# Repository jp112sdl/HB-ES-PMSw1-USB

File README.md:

# HB-ES-PMSw1-USB
Homebrew Homematic USB Strom-/Spannungsmesser mit INA219

Benötigt [JP-HB-Devices Addon mind. V 4.2](https://github.com/jp112sdl/JP-HB-Devices-addon/releases)

In der Arduino IDE muss noch folgende Lib eingebunden werden:
- https://github.com/jp112sdl/INA219_WE

### Aktueller Stand (14.03.2021):
- CCU Unterstützung bereitgestellt (Addon V 4.2)
- Sketch lauffähig

### schematischer Schaltungsaufbau

###  🚧 PCB - WORK IN PROGRESS

Projekt-Thread im HomeMatic-Forum: https://homematic-forum.de/forum/viewtopic.php?f=76&t=66307

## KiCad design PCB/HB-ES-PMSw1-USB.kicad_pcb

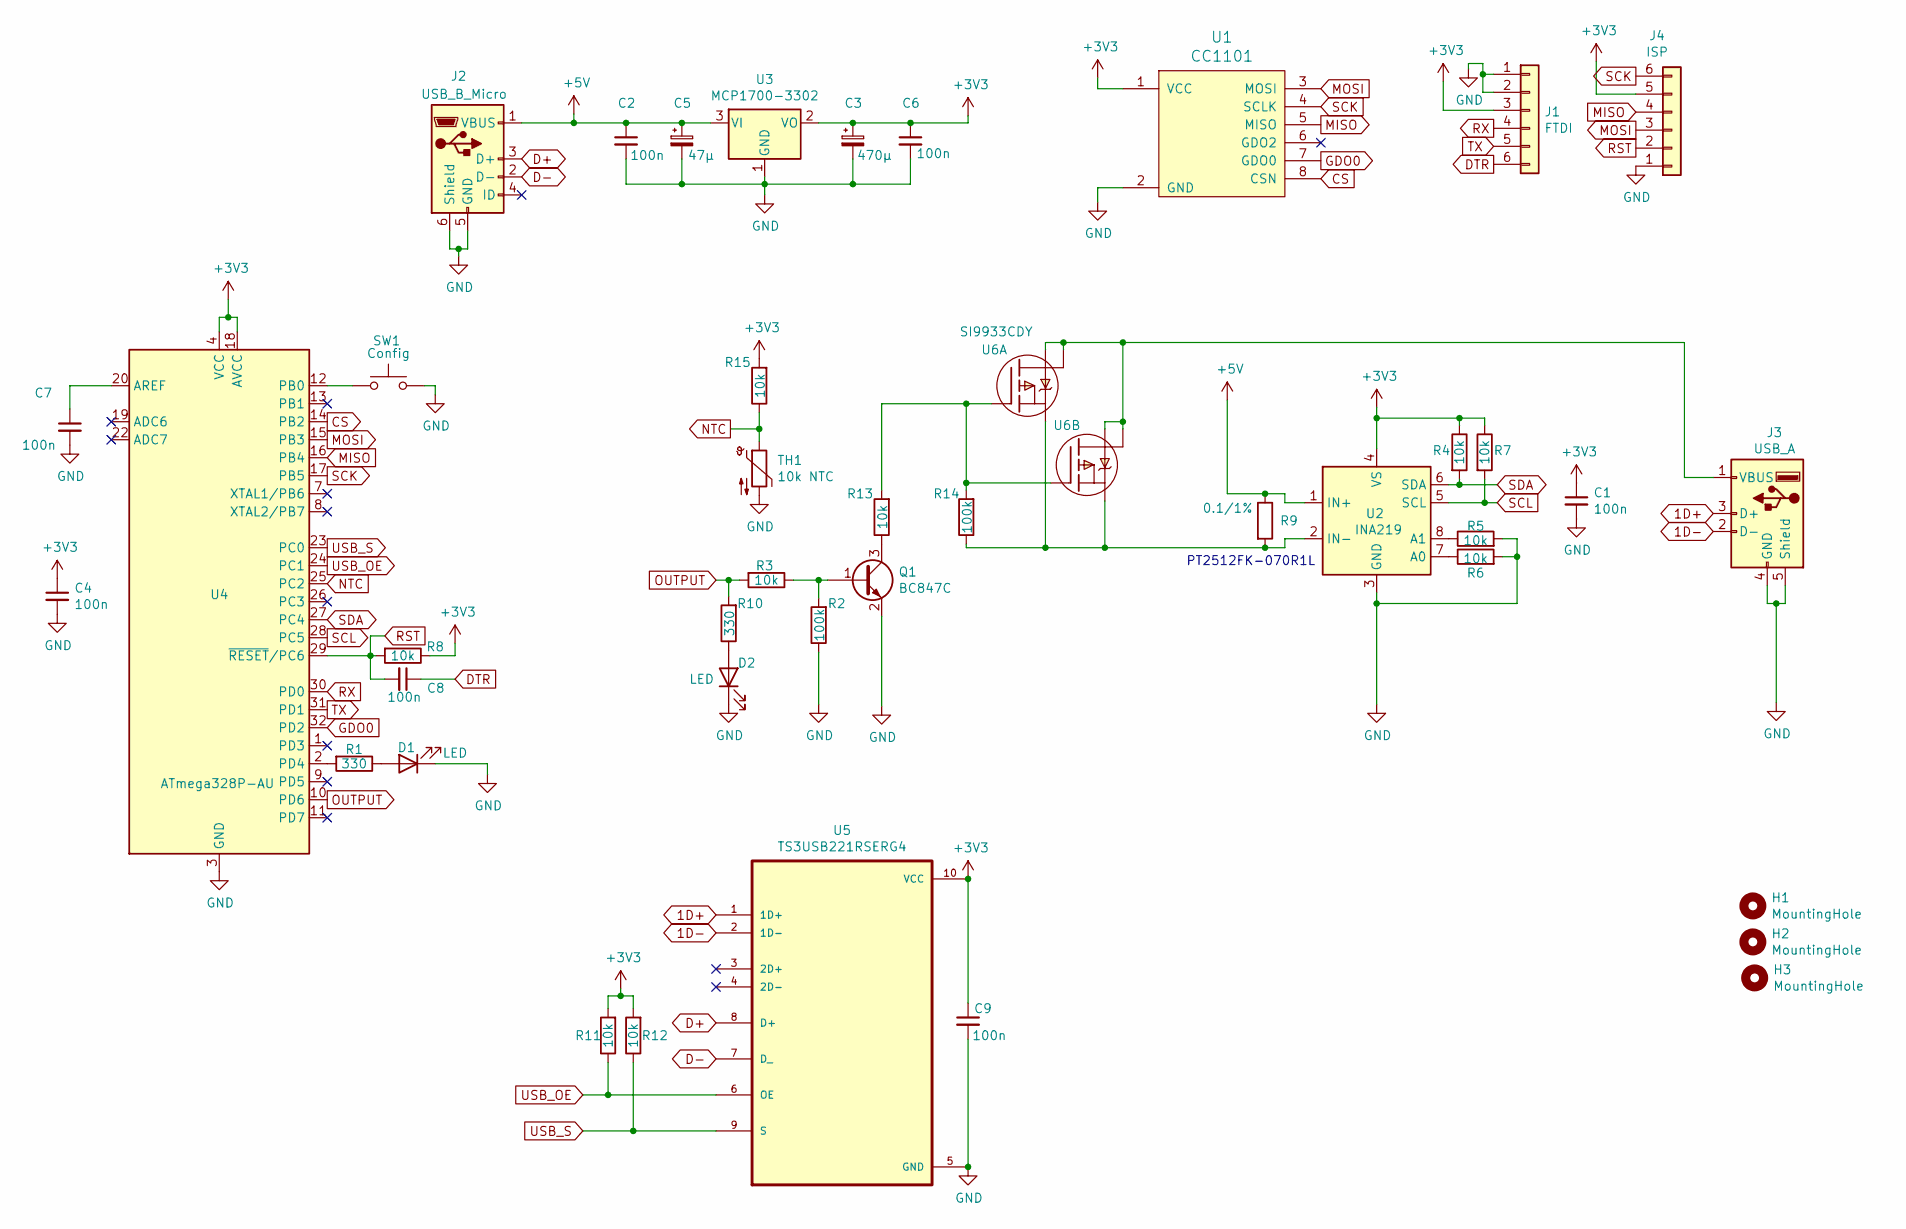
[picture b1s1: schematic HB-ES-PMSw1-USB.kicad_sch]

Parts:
C1, C2, C4, C6, C7, C8, C9: 100n; C_0805_2012Metric_Pad1.15x1.40mm_HandSolder
C3: 470µ; CP_Elec_8x10.5
C5: 47µ; CP_Elec_8x5.4
D1, D2: LED; LED_0805_2012Metric_Pad1.15x1.40mm_HandSolder
H1, H2, H3: MountingHole; MountingHole_2.7mm_M2.5
J1: FTDI; PinHeader_1x06_P2.54mm_Vertical
J2: USB_B_Micro; USB_Micro-B_Molex-105017-0001
J3: USB_A
J4: ISP; PinPads_ISP
Q1: BC847C; SOT-23
R1, R10: 330; R_0805_2012Metric_Pad1.15x1.40mm_HandSolder
R2, R14: 100k; R_0805_2012Metric_Pad1.15x1.40mm_HandSolder
R3, R4, R5, R6, R7, R8, R11, R12, R13, R15: 10k; R_0805_2012Metric_Pad1.15x1.40mm_HandSolder
R9: 0.1/1%; R_2512_6332Metric_Pad1.52x3.35mm_HandSolder
SW1: Config; SW_PUSH_6mm_H5mm
TH1: 10k NTC; R_0805_2012Metric_Pad1.15x1.40mm_HandSolder
U1: CC1101; CC1101_SMD
U2: INA219; SOT-23-8
U3: MCP1700-3302; SOT-23
U4: ATmega328P-AU; TQFP-32_7x7mm_P0.8mm
U5: TS3USB221RSERG4; SON50P300X300X100-11N
U6: SI9933CDY; SO8-2

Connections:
1D+: J3.3 (D+), U5.1 (1D+)
1D-: J3.2 (D-), U5.2 (1D-)
+3V3: C1.1, C3.1, C4.1, C6.1, C9.1, J1.3, J4.5, R4.1, R7.1, R8.1, R11.2, R12.2, R15.2, U1.1 (VCC), U2.4 (VS), U3.2 (VO), U4.4 (VCC), U4.6 (VCC), U4.18 (AVCC), U5.10 (VCC)
+5V: C2.1, C5.1, J2.1 (VBUS), R9.1, U2.1 (IN+), U3.3 (VI)
CS: U1.8 (CSN), U4.14 (PB2)
D+: J2.3 (D+), U5.8 (D+)
D-: J2.2 (D-), U5.7 (D_)
DTR: C8.1, J1.6
GDO0: U1.7 (GDO0), U4.32 (PD2)
GND: C1.2, C2.2, C3.2, C4.2, C5.2, C6.2, C7.2, C9.2, D1.1 (K), D2.1 (K), J1.1, J1.2, J2.5 (GND), J2.6 (Shield), J3.4 (GND), J3.5 (Shield), J4.1, Q1.2 (E), R2.1, R5.2, R6.2, SW1.2, TH1.2, U1.2 (GND), U2.3 (GND), U3.1 (GND), U4.3 (GND), U4.5 (GND), U4.21 (GND), U5.5 (GND)
MISO: J4.4, U1.5 (MISO), U4.16 (PB4)
MOSI: J4.3, U1.3 (MOSI), U4.15 (PB3)
NTC: R15.1, TH1.1, U4.25 (PC2)
unnamed: C7.1, U4.20 (AREF)
unnamed: D1.2 (A), R1.1
unnamed: D2.2 (A), R10.1
unnamed: J3.1 (VBUS), U6.5, U6.6, U6.7, U6.8
unnamed: Q1.1 (B), R2.2, R3.1
unnamed: Q1.3 (C), R13.1
unnamed: R1.2, U4.2 (PD4)
unnamed: R5.1, U2.8 (A1)
unnamed: R6.1, U2.7 (A0)
unnamed: R13.2, R14.2, U6.2, U6.4
unnamed: R9.2, R14.1, U2.2 (IN-), U6.1, U6.3
unnamed: SW1.1, U4.12 (PB0)
OUTPUT: R3.2, R10.2, U4.10 (PD6)
RST: C8.2, J4.2, R8.2, U4.29 (~RESET/PC6)
RX: J1.4, U4.30 (PD0)
SCK: J4.6, U1.4 (SCLK), U4.17 (PB5)
SCL: R7.2, U2.5 (SCL), U4.28 (PC5)
SDA: R4.2, U2.6 (SDA), U4.27 (PC4)
TX: J1.5, U4.31 (PD1)
USB_OE: R11.1, U4.24 (PC1), U5.6 (OE)
USB_S: R12.1, U4.23 (PC0), U5.9 (S)

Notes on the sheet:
PT2512FK-070R1L

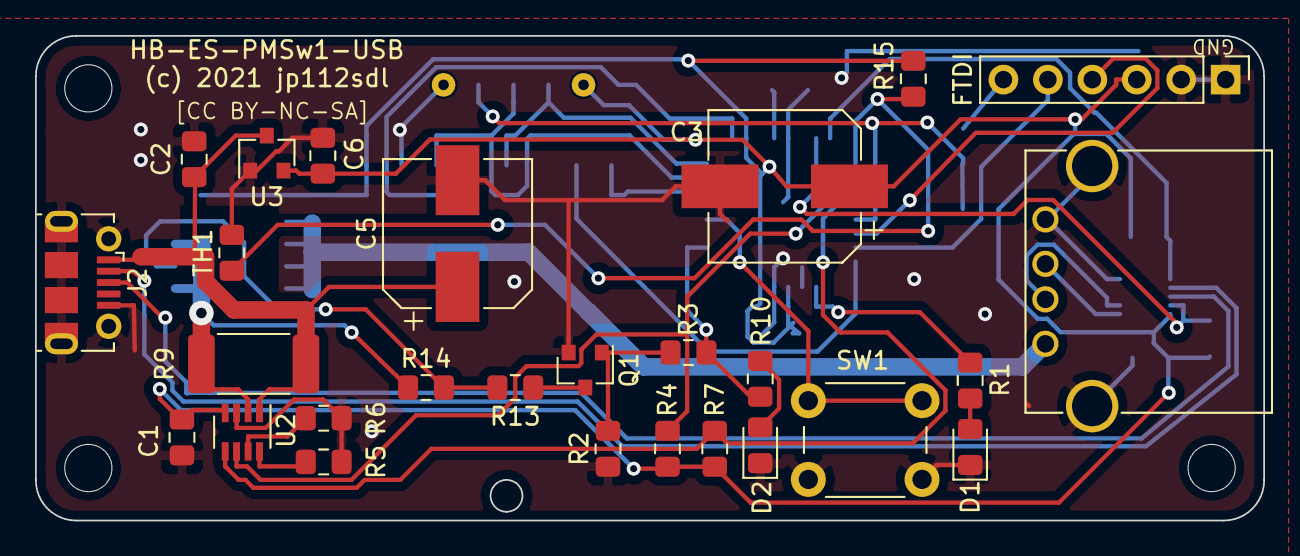
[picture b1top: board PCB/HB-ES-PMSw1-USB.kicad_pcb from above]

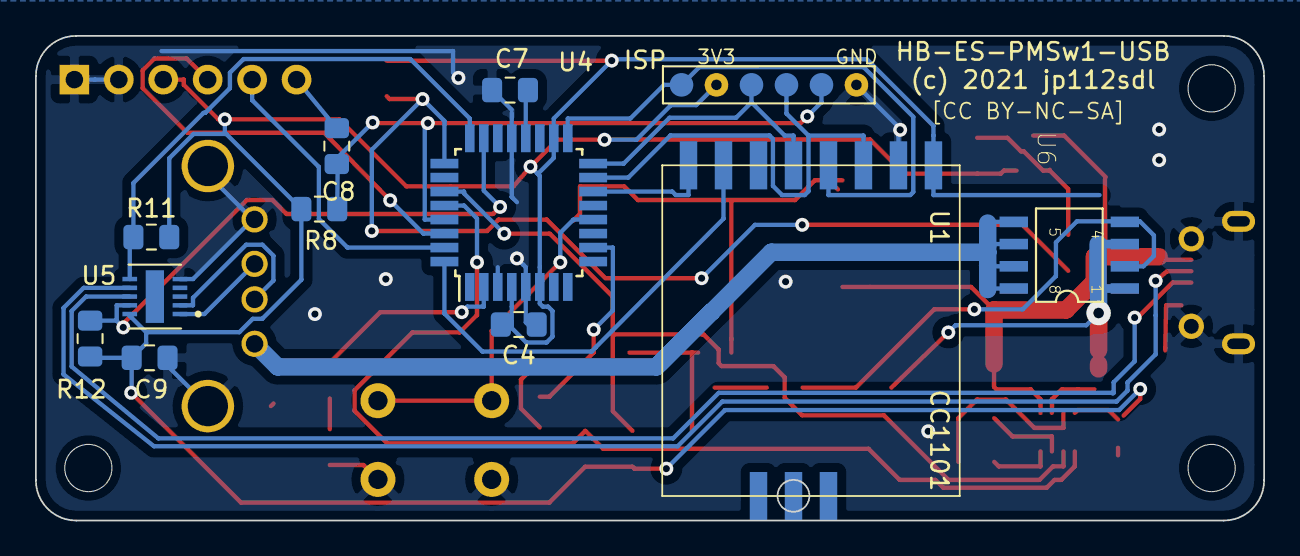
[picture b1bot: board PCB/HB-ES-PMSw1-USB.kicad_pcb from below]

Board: 2 copper layers, 70.2 x 27.7 mm, 42 parts (12 on the bottom side), 34 nets.

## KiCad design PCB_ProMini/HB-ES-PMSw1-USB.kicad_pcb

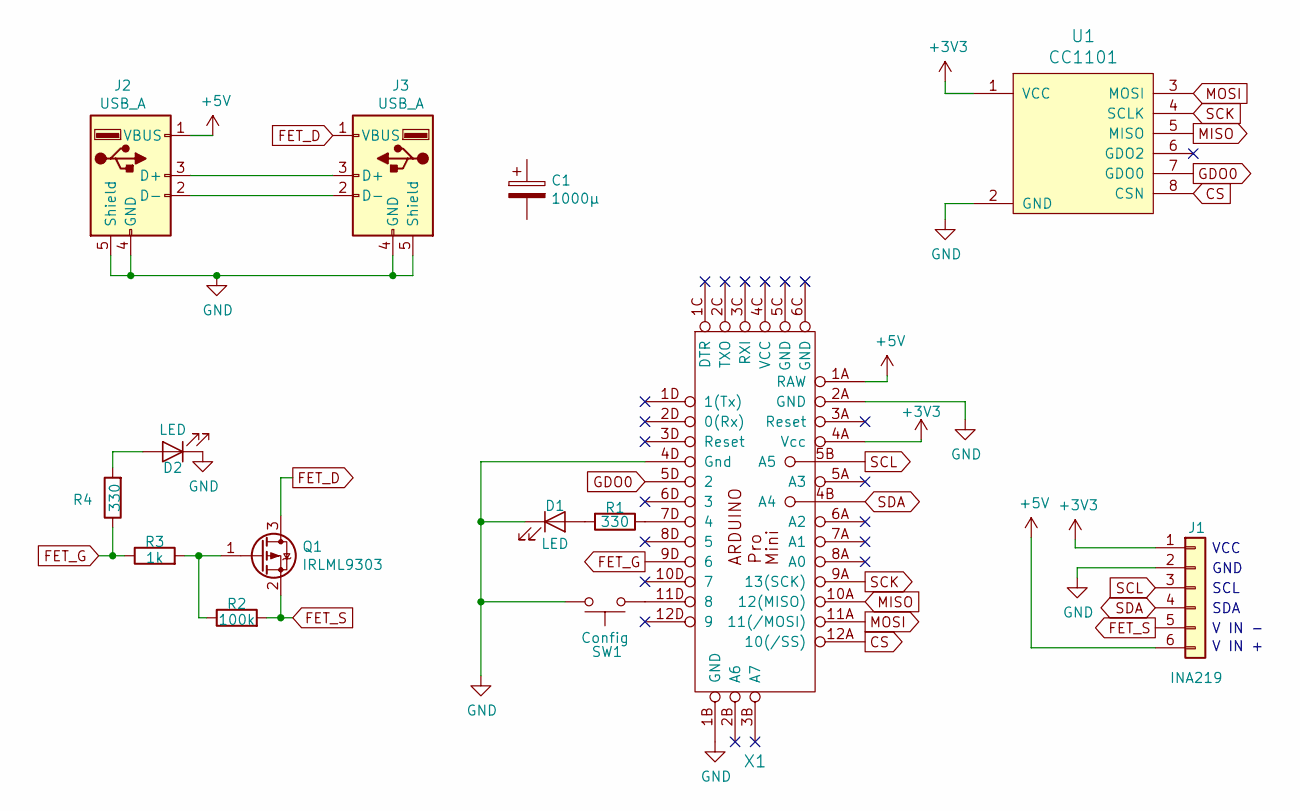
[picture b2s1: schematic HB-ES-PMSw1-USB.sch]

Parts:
C1: 1000µ; CP_Axial_L29.0mm_D13.0mm_P35.00mm_Horizontal
D1, D2: LED; LED_D3.0mm
J1: INA219; PinHeader_1x06_P2.54mm_Vertical
J2, J3: USB_A
Q1: IRLML9303; TO-220-3_Horizontal_TabDown
R1, R4: 330; R_Axial_DIN0204_L3.6mm_D1.6mm_P7.62mm_Horizontal
R2: 100k; R_Axial_DIN0204_L3.6mm_D1.6mm_P2.54mm_Vertical
R3: 1k; R_Axial_DIN0204_L3.6mm_D1.6mm_P2.54mm_Vertical
SW1: Config; SW_PUSH_6mm_H5mm
U1: CC1101
X1: Arduino_Pro_Mini

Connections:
+3V3: J1.1, U1.1 (VCC), X1.4A (Vcc)
+5V: J1.6, J2.1 (VBUS), X1.1A (RAW)
CS: U1.8 (CSN), X1.12A (10(/SS))
FET_D: J3.1 (VBUS), Q1.3 (D)
FET_G: R3.1, R4.1, X1.9D (6)
FET_S: J1.5, Q1.2 (S), R2.2
GDO0: U1.7 (GDO0), X1.5D (2)
GND: D1.1 (K), D2.1 (K), J1.2, J2.4 (GND), J2.5 (Shield), J3.4 (GND), J3.5 (Shield), SW1.2, U1.2 (GND), X1.1B (GND), X1.2A (GND), X1.4D (Gnd)
MISO: U1.5 (MISO), X1.10A (12(MISO))
MOSI: U1.3 (MOSI), X1.11A (11(/MOSI))
unnamed: D1.2 (A), R1.2
unnamed: D2.2 (A), R4.2
unnamed: J2.2 (D-), J3.2 (D-)
unnamed: J2.3 (D+), J3.3 (D+)
unnamed: Q1.1 (G), R2.1, R3.2
unnamed: R1.1, X1.7D (4)
unnamed: SW1.1, X1.11D (8)
SCK: U1.4 (SCLK), X1.9A (13(SCK))
SCL: J1.3, X1.5B (A5)
SDA: J1.4, X1.4B (A4)

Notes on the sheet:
GND
VCC
SCL
SDA
V IN +
V IN -

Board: 2 copper layers, 13 parts (2 on the bottom side), 20 nets, no tracks yet.

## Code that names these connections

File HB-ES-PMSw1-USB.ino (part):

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#define INVERT_SWITCH_PIN   true //true = ACTIVE LOW
#define BUTTON_PIN          8
#define LED_PIN             4
#define NTC                A2

#define USB_OE             A1
#define USB_S              A0

// number of available peers per channel
#define PEERS_PER_SWCHANNEL     8
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class TS3USB221 {
public:
  void init() {
    pinMode(USB_OE, OUTPUT);
    pinMode(USB_S,  OUTPUT);

    //set initial state
    digitalWrite(USB_OE, HIGH);
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
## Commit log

2021-03-07 minor changes
2021-03-14 update peering
2021-03-14 add wiring
2022-01-12 update kicad

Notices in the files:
HB-ES-PMSw1-USB.ino:
2017-10-24 papa Creative Commons - http://creativecommons.org/licenses/by-nc-sa/3.0/de
2021-03-06 jp112sdl Creative Commons - http://creativecommons.org/licenses/by-nc-sa/3.0/de
PCB/HB-ES-PMSw1-USB.kicad_pcb:
[CC BY-NC-SA]
(c) 2021 jp112sdl
